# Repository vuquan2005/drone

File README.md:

# Đồ án Quadrotor sử dụng STM32

Repository chứa firmware, thiết kế phần cứng, tài liệu nghiên cứu và báo cáo
cho đồ án quadrotor. Firmware đã có đọc IMU, nhận RC qua CRSF, điều khiển tốc
độ góc, mixer và arm/failsafe; gain và ánh xạ motor hiện chỉ dành cho thử trên
bộ gá, chưa hiệu chuẩn để bay.

- [Firmware](firmware/README.md): hướng dẫn bắt đầu, build và nạp.
- [Firmware drone](firmware/drone/README.md): chế độ vận hành và giao tiếp phần cứng.
- [Debug và thử trên board](firmware/drone/DEBUG.md) · [Công cụ RTT](tools/rtt/README.md).
- [Phần cứng](hardware/kicad/Quadrotor_Wiring.kicad_pro) · [Tài liệu nghiên cứu](docs/README.md) · [Công cụ](tools/README.md).
- `report/`: báo cáo LaTeX
- `experiments/`: cấu hình, dữ liệu và kết quả đo.

Thuật toán trong `firmware/drone/Control/` độc lập HAL và do `App/` điều phối.
Kiểm chứng bằng kiểm thử thuật toán nhỏ trên máy tính và đo trên board/bộ gá;
kế hoạch hiện tại không triển khai mô phỏng vòng kín hoặc SITL. Xem
[kiến trúc firmware](firmware/drone/ARCHITECTURE.md) và
[quy trình làm việc nhóm](CONTRIBUTING.md).

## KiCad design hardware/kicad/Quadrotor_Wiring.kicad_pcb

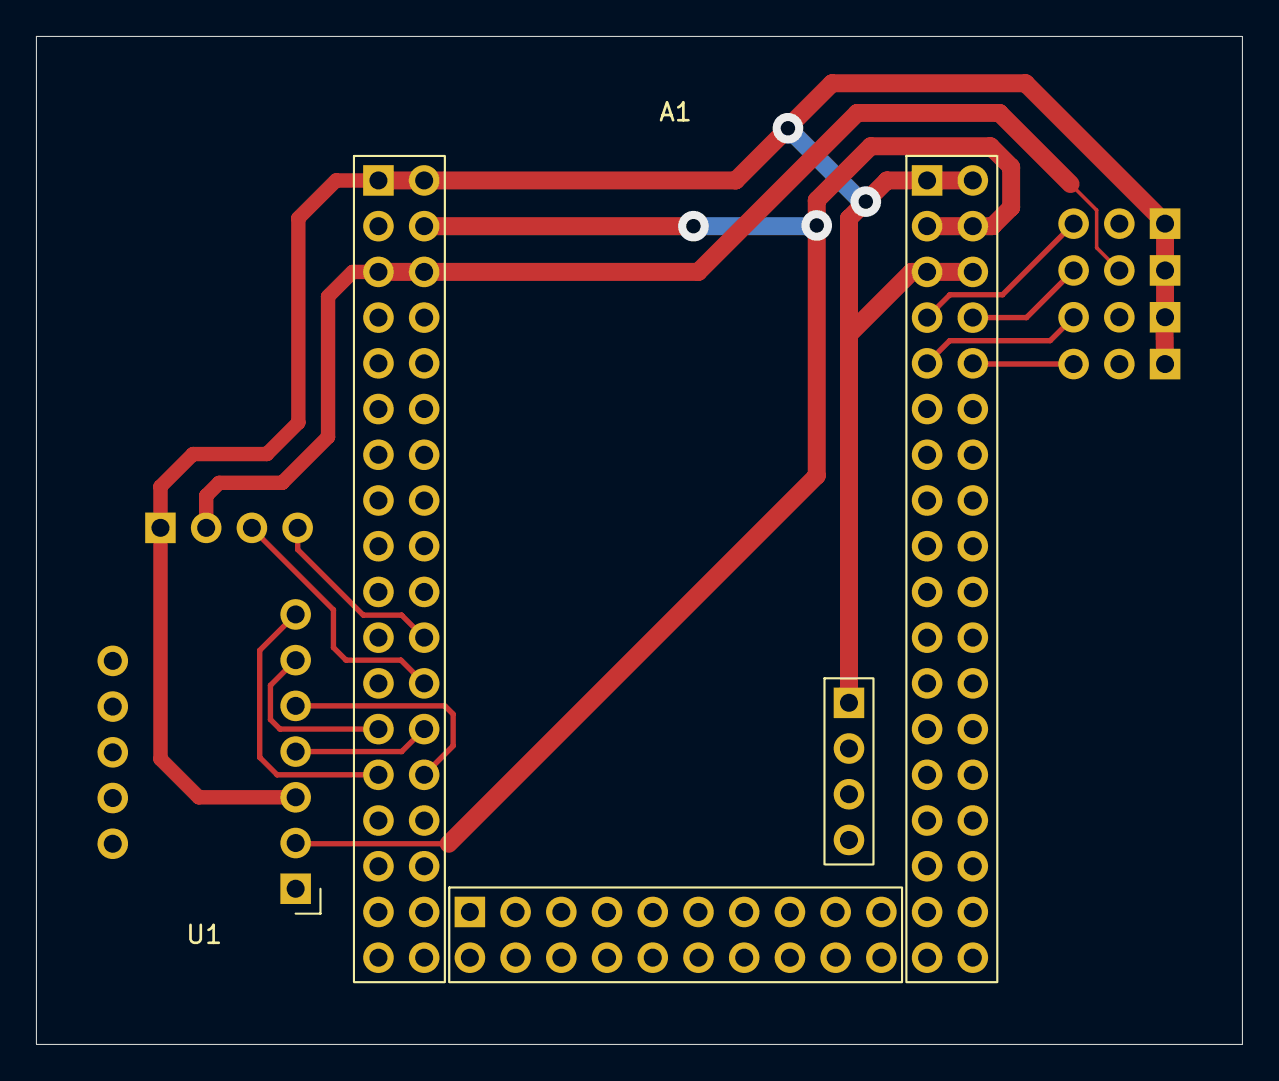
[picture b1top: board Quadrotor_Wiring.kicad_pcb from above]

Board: 2 copper layers, 67.0 x 56.0 mm, 7 parts (0 on the bottom side), 13 nets.

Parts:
A1: STM32_DevKit; STM32F103VET6_DevKit_P2.54mm_Sockets
J1, J2, J3, J4: ESC Header; ESC_PWM_Header_1x03_P2.54mm_Vertical
U1: BMI160_Module; BMI160_Module_7+5_P2.54mm_W10.16mm
U2: SB_Nano_Receiver; ELRS_Header_1x04_P2.54mm_Vertical

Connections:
/+3V3: A1.3V3_1 (3V3), A1.3V3_2 (3V3), A1.3V3_3 (3V3), A1.3V3_4 (3V3), U1.2 (3V3)
/+5V: A1.5V_1 (5V), A1.5V_2 (5V), J2.7 (BEC), U2.3 (5V)
/ELRS_TX_STM32_RX: A1.PA3 (A3), U2.2 (TX)
/ESC1_PWM: A1.PB9 (B9), J1.6 (PWM)
/ESC2_PWM: A1.PB8 (B8), J2.6 (PWM)
/ESC3_PWM: A1.PB7 (B7), J3.6 (PWM)
/ESC4_PWM: A1.PB6 (B6), J4.6 (PWM)
/IMU_CS: A1.PA4 (A4), U1.6 (CS)
/SPI1_MISO: A1.PA6 (A6), U1.7 (SAO/MISO)
/SPI1_MOSI: A1.PA7 (A7), U1.5 (SDA/MOSI)
/SPI1_SCK: A1.PA5 (A5), U1.4 (SCL/SCLK)
/STM32_TX_ELRS_RX: A1.PA2 (A2), U2.1 (RX)
GND: A1.GND1 (GND), A1.GND2 (GND), A1.GND3 (GND), A1.GND4 (GND), A1.GND5 (GND), A1.GND6 (GND), A1.GND7 (GND), J1.8 (GND), J2.8 (GND), J3.8 (GND), J4.8 (GND), U1.3 (GND), U2.4 (GND)

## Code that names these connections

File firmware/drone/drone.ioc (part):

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Mcu.Name=STM32F103V(C-D-E)Tx
Mcu.Package=LQFP100
Mcu.UserName=STM32F103VETx
PA13.Mode=Serial_Wire
PA13.Signal=SYS_JTMS-SWDIO
PA14.Mode=Serial_Wire
PA14.Signal=SYS_JTCK-SWCLK
PA2.GPIOParameters=GPIO_Label
PA2.GPIO_Label=RECEIVER_TX
PA2.Mode=Asynchronous
PA2.Signal=USART2_TX
PA3.GPIOParameters=GPIO_Label
PA3.GPIO_Label=RECEIVER_RX
PA3.Mode=Asynchronous
PA3.Signal=USART2_RX
PA4.GPIOParameters=PinState,GPIO_Label
PA4.GPIO_Label=IMU_CS
PA4.PinState=GPIO_PIN_SET
PA4.Signal=GPIO_Output
PA5.Mode=Full_Duplex_Master
PA5.Signal=SPI1_SCK
PA6.Mode=Full_Duplex_Master
PA6.Signal=SPI1_MISO
PA7.Mode=Full_Duplex_Master
PA7.Signal=SPI1_MOSI
PB12.GPIOParameters=PinState,GPIO_Label
PB12.GPIO_Label=FLASH_CS
PB12.PinState=GPIO_PIN_SET
PB12.Signal=GPIO_Output
PB13.Mode=Full_Duplex_Master
PB13.Signal=SPI2_SCK
PB14.Mode=Full_Duplex_Master
PB14.Signal=SPI2_MISO
PB15.Mode=Full_Duplex_Master
PB15.Signal=SPI2_MOSI
PB6.GPIOParameters=GPIO_Label
PB6.GPIO_Label=MOTOR_3
PB6.Signal=S_TIM4_CH1
PB7.GPIOParameters=GPIO_Label
PB7.GPIO_Label=MOTOR_4
PB7.Signal=S_TIM4_CH2
PB8.GPIOParameters=GPIO_Label
PB8.GPIO_Label=MOTOR_1
PB8.Signal=S_TIM4_CH3
PB9.GPIOParameters=GPIO_Label
PB9.GPIO_Label=MOTOR_2
PB9.Signal=S_TIM4_CH4
PE3.GPIOParameters=GPIO_Label
PE3.GPIO_Label=STATUS_LED
PE3.Signal=GPIO_Output
RCC.SYSCLKFreq_VALUE=72000000
RCC.SYSCLKSource=RCC_SYSCLKSOURCE_PLLCLK
board=custom
